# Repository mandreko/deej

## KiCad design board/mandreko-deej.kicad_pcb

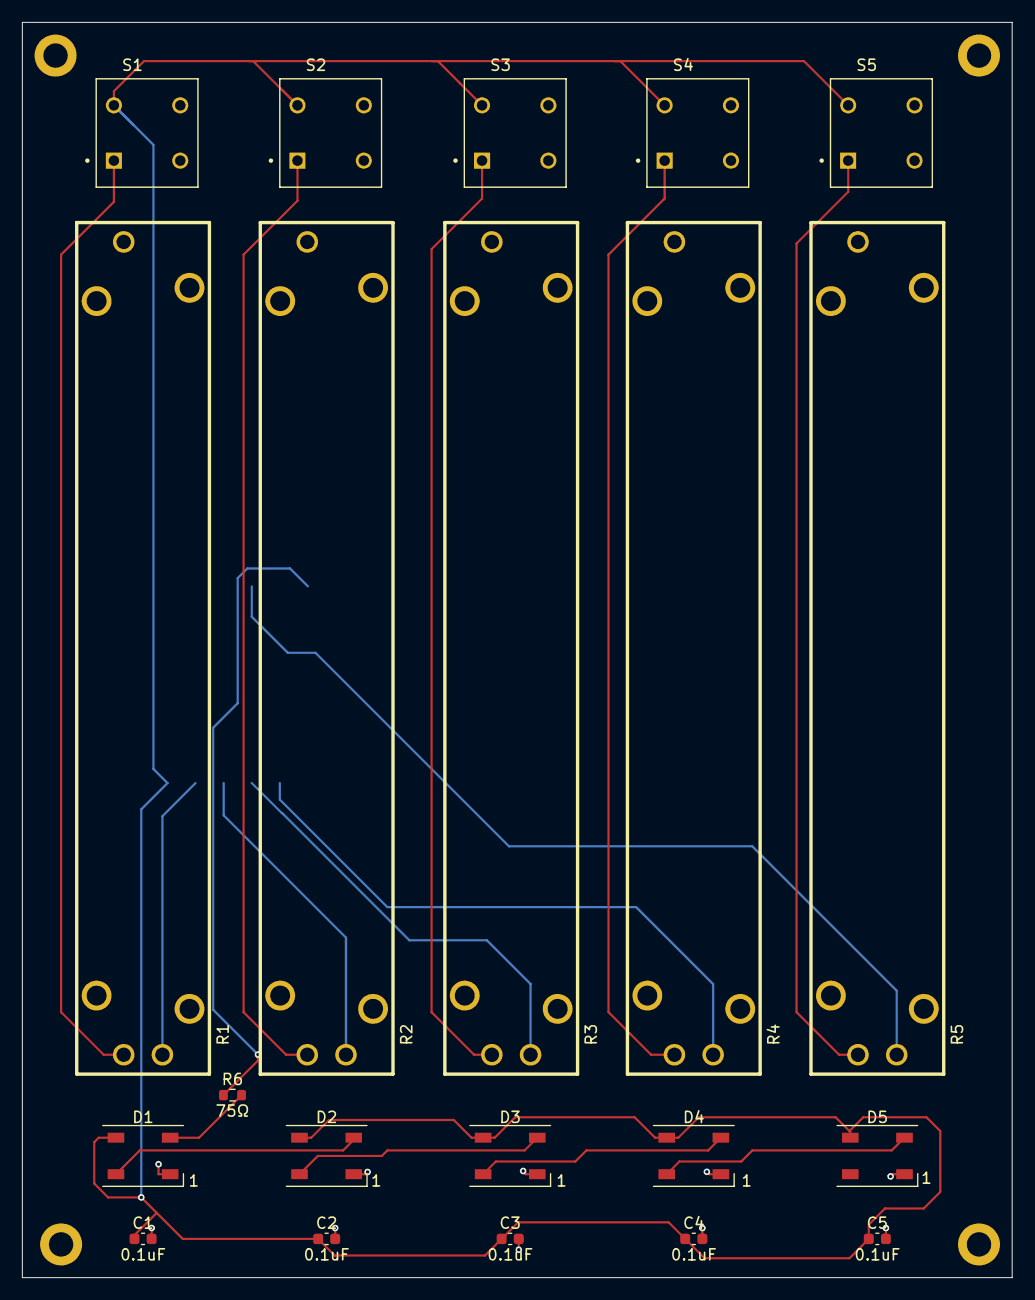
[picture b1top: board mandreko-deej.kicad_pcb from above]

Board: 2 copper layers, 89.5 x 113.5 mm, 26 parts (1 on the bottom side), 18 nets.

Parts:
BottomLeftMountingHole: MountingHole_2.2mm_M2_DIN965_Pad
BottomRightMountingHole: MountingHole_2.2mm_M2_DIN965_Pad
C1, C2, C3, C4, C5: 0.1uF; C_0603_1608Metric
D1, D2, D3, D4, D5: WS2812B; LED_WS2812B_PLCC4_5.0x5.0mm_P3.2mm
R1, R2, R3, R4, R5: PTA6043-2015DPB103; PTA6043-2015DP-B103
R6: 75Ω; R_0603_1608Metric
S1, S2, S3, S4, S5: PVA1EEH1; SW_PVA1EEH1
TopLeftMountingHole: MountingHole_2.2mm_M2_DIN965_Pad
TopRightMountingHole: MountingHole_2.2mm_M2_DIN965_Pad
U1: ProMicroC

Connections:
5V: C1.1, C2.1, C3.1, C4.1, C5.1, D1.1 (VDD), D2.1 (VDD), D3.1 (VDD), D4.1 (VDD), D5.1 (VDD), S1.2, S2.2, S3.2, S4.2, S5.2, U1.21 (5V)
A0: R4.2, U1.17 (A0)
A1: R3.2, U1.18 (A1)
A2: R2.2, U1.19 (A2)
A3: R1.2, U1.20 (A3)
A6: R5.2, U1.7 (D4/A6)
A7: R6.1, U1.9 (D6/A7)
GND: BottomLeftMountingHole.1, BottomRightMountingHole.1, C1.2, C2.2, C3.2, C4.2, C5.2, D1.3 (VSS), D2.3 (VSS), D3.3 (VSS), D4.3 (VSS), D5.3 (VSS), R1.3, R2.3, R3.3, R4.3, R5.3, TopLeftMountingHole.1, TopRightMountingHole.1, U1.3 (GND), U1.4 (GND), U1.23 (GND)
unnamed: D1.4 (DIN), R6.2
unnamed: D1.2 (DOUT), D2.4 (DIN)
unnamed: D2.2 (DOUT), D3.4 (DIN)
unnamed: D3.2 (DOUT), D4.4 (DIN)
unnamed: D4.2 (DOUT), D5.4 (DIN)
unnamed: R1.1, S1.1
unnamed: R2.1, S2.1
unnamed: R3.1, S3.1
unnamed: R4.1, S4.1
unnamed: R5.1, S5.1

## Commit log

2024-03-21 Initial addition of custom PCB for deej board
2024-03-30 Fixed footprints of sliders, after verifying original was incorrect. Routed wires. Generated fabrication outputs
2024-04-11 Fixed board wiring error. Regenerated fabrication files. Added PlatformIO project with LED code. Added STEP of the board 3d model.
2025-03-20 Added case files
